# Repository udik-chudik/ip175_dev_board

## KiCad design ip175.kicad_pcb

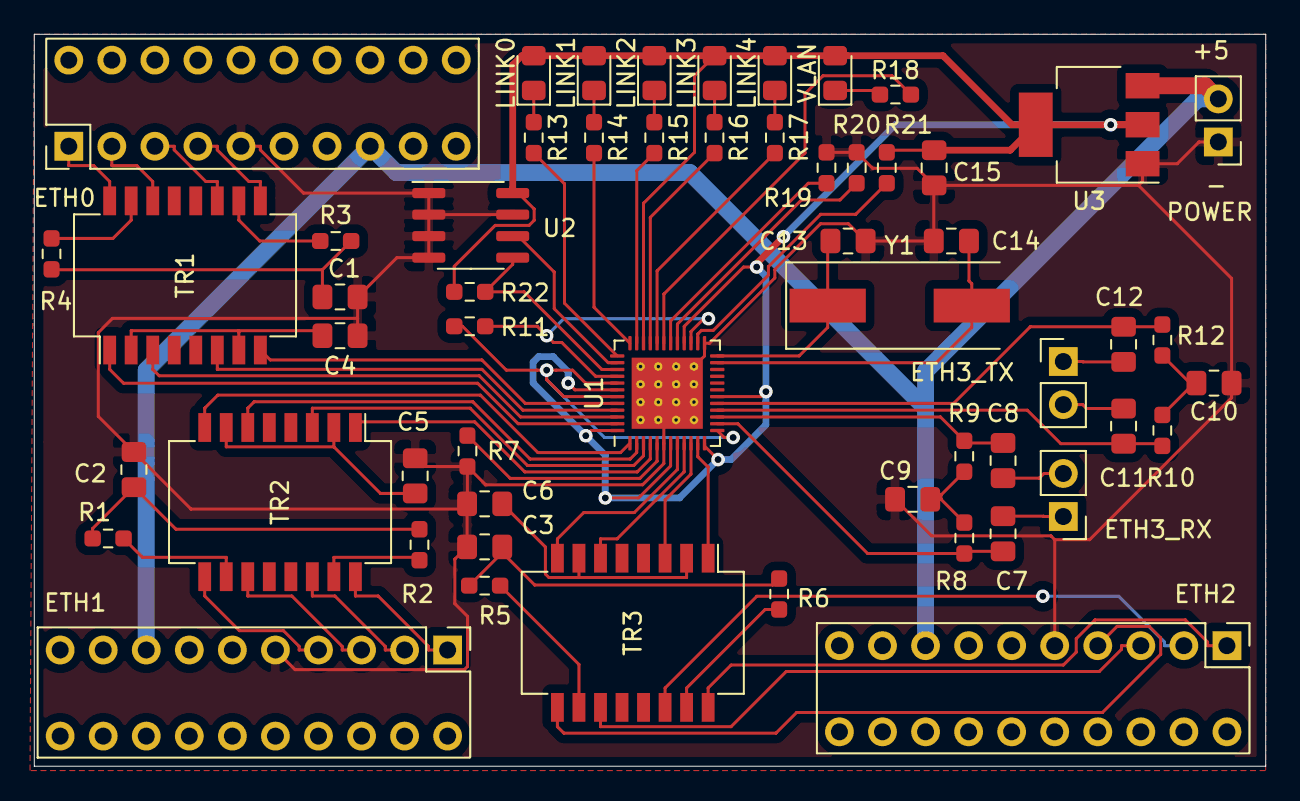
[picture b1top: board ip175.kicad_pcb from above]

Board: 2 copper layers, 72.6 x 43.2 mm, 56 parts (0 on the bottom side), 71 nets.

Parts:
C1, C2, C3: 1000; C_0805_2012Metric_Pad1.18x1.45mm_HandSolder
C4, C5, C6: 10n; C_0805_2012Metric_Pad1.18x1.45mm_HandSolder
C7, C8, C9, C10, C11, C12: 100n; C_0805_2012Metric_Pad1.18x1.45mm_HandSolder
C13, C14: 22; C_0805_2012Metric_Pad1.18x1.45mm_HandSolder
C15: C_Small; C_0805_2012Metric_Pad1.18x1.45mm_HandSolder
ETH0, ETH1, ETH2: Conn_02x10_Counter_Clockwise; FR_Conn
ETH3_RX, ETH3_TX: Conn_01x02_Male; PinHeader_1x02_P2.54mm_Vertical
LINK0, LINK1, LINK2, LINK3, LINK4: LED_Small_ALT; LED_0805_2012Metric_Pad1.15x1.40mm_HandSolder
POWER: Conn_01x02_Male; PinHeader_1x02_P2.54mm_Vertical
R1, R2, R3, R4, R5, R6: 75; R_0603_1608Metric_Pad0.98x0.95mm_HandSolder
R7, R13, R14, R15, R16, R17, R18, R19, R20, R21: R_Small; R_0603_1608Metric_Pad0.98x0.95mm_HandSolder
R8, R9, R10, R12: 50; R_0603_1608Metric_Pad0.98x0.95mm_HandSolder
R11: R_or_Bread; R_0603_1608Metric_Pad0.98x0.95mm_HandSolder
R22: 4.7K; R_0603_1608Metric_Pad0.98x0.95mm_HandSolder
TR1, TR2, TR3: PT61017PEL; Transformer_Ethernet_Bourns_PT61017PEL
U1: ip175; QFN-48-1EP_6x6mm_P0.4mm_EP4.2x4.2mm_ThermalVias
U2: at24c16; SOIC-8_3.9x4.9mm_P1.27mm
U3: AMS1117-3.3; SOT-223-3_TabPin2
VLAN: LED_Small_ALT; LED_0805_2012Metric_Pad1.15x1.40mm_HandSolder
Y1: 25MHz; Crystal_SMD_HC49-SD

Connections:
+3V3: C15.2, LINK0.2, LINK1.2, LINK2.2, LINK3.2, LINK4.2, R21.1, R22.1, U1.7, U1.12, U1.18, U1.28, U1.34, U1.42, U1.48, U2.8, U3.2, VLAN.2
+5V: ETH0.8, ETH1.8, ETH2.8, POWER.2, U3.3
GND: C1.2, C2.2, C3.2, C4.2, C5.2, C6.2, C9.1, C10.1, C13.2, C14.2, C15.1, ETH0.5, ETH1.5, ETH2.5, POWER.1, R7.1, R19.1, R20.1, U1.6, U1.25, U1.49, U2.1, U2.2, U2.3, U2.4, U2.7, U3.1
MDC: U1.38, U2.6
MDIO: R22.2, U1.39, U2.5
unnamed: C1.1, R3.1, R4.1
unnamed: C2.1, R1.1, R2.1
unnamed: C3.1, R5.1, R6.1
unnamed: C4.1, TR1.2, TR1.7
unnamed: C5.1, TR2.2, TR2.7
unnamed: C6.1, TR3.2, TR3.7
unnamed: C7.1, ETH3_RX.1
unnamed: C7.2, R8.2, U1.14
unnamed: C8.1, R9.2, U1.15
unnamed: C8.2, ETH3_RX.2
unnamed: C9.2, R8.1, R9.1
unnamed: C10.2, R10.1, R12.1
unnamed: C11.1, R10.2, U1.16
unnamed: C11.2, ETH3_TX.2
unnamed: C12.1, R12.2, U1.17
unnamed: C12.2, ETH3_TX.1
unnamed: C13.1, U1.24, Y1.1
unnamed: C14.1, U1.23, Y1.2
unnamed: LINK0.1, R13.1
unnamed: LINK1.1, R14.1
unnamed: LINK2.1, R15.1
unnamed: LINK3.1, R16.1
unnamed: LINK4.1, R17.1
unnamed: R18.1, VLAN.1
unnamed: ETH0.1, TR1.16
unnamed: ETH0.2, TR1.14
unnamed: ETH0.3, TR1.11
unnamed: ETH0.4, TR1.9
unnamed: ETH1.1, TR2.16
unnamed: ETH1.2, TR2.14
unnamed: ETH1.3, TR2.11
unnamed: ETH1.4, TR2.9
unnamed: ETH2.1, TR3.16
unnamed: ETH2.2, TR3.14
unnamed: ETH2.3, TR3.11
unnamed: ETH2.4, TR3.9
unnamed: R1.2, TR2.10
unnamed: R2.2, TR2.15
unnamed: R3.2, TR1.10
unnamed: R4.2, TR1.15
unnamed: R5.2, TR3.10
unnamed: R6.2, TR3.15
unnamed: R7.2, U1.5
unnamed: R11.1, U1.13, U1.41, U1.43
unnamed: R11.2, U1.27, U1.40
unnamed: R13.2, U1.37
unnamed: R14.2, U1.36
unnamed: R15.2, U1.35
unnamed: R16.2, U1.33
unnamed: R17.2, U1.32
unnamed: R18.2, U1.31
unnamed: R19.2, U1.30
unnamed: R20.2, U1.29
unnamed: R21.2, U1.26
unnamed: TR1.1, U1.47
unnamed: TR1.3, U1.46
unnamed: TR1.6, U1.45
unnamed: TR1.8, U1.44
unnamed: TR2.1, U1.4
unnamed: TR2.3, U1.3
unnamed: TR2.6, U1.2
unnamed: TR2.8, U1.1
unnamed: TR3.1, U1.11
unnamed: TR3.3, U1.10
unnamed: TR3.6, U1.9
unnamed: TR3.8, U1.8

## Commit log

2020-11-07 Закончили со схемой (нужно перепроверить) + предварительная разводка платы
2020-11-09 Закончили разводку платы, отправили в производство
